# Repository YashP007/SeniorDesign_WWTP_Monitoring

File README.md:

# Advancing Wastewater Monitoring through Engineered Biological Sensors

**Yash Patel, Kara Walp**  
Department of Biomedical Engineering, Senior Design, Group 4 (2024–2025)  
Advisors: Rabia Tuğçe Yazicigil Kirby (BME, ECE), Miguel Jimenez (BME, MSE)

---

## Abstract
Effective industrial wastewater monitoring is critical for regulatory compliance and process optimization. However, traditional analytical techniques such as high-performance liquid chromatography (HPLC) are costly, require centralized facilities, and introduce significant latency between sampling and actionable results. Advances in synthetic biology have enabled the engineering of microbial whole-cell biosensors capable of detecting environmental contaminants with high specificity and rapid response times. Yet, practical deployment is limited by microbial instability in harsh environments and the lack of compact, low-power systems for low-signal optical outputs.

This work presents a deployable biosensing platform integrating a microbe housing and a low-power optical detection system designed for in situ wastewater monitoring. A membrane-based chamber enhances microbial viability by modulating nutrient and oxygen diffusion while preventing environmental microbial egress. Optical detection of luminescence was achieved using an analog front end with noise shaping and oversampling, enabling quantification of multiple biosensor outputs.

Experimental validation demonstrated improved microbial stability with Escherichia coli, extending viability beyond typical single-use constraints. The integrated system successfully captured optical responses from biosensors at environmentally relevant analyte concentrations. These findings highlight a promising pathway toward continuous, real-time wastewater monitoring using whole-cell biosensors. Future work must address challenges related to thermal robustness and variable contaminant backgrounds to achieve broader commercial deployment.

Contents:
Aim 1 - Creating a Microbe Housing for Deployment in Wastewater Treatment Plants
Aim 2 - Creating a Deployable Optical Detection Circuit

1. STL Files for Microbe Housing
2. Image Procesing Code for evaluating the microbe housing using the plate reader
3. KiCAD Files for Final Optical Sensing Circuit
4. Optical Sensing Circuit ESP32-C3 Microcontroller Program

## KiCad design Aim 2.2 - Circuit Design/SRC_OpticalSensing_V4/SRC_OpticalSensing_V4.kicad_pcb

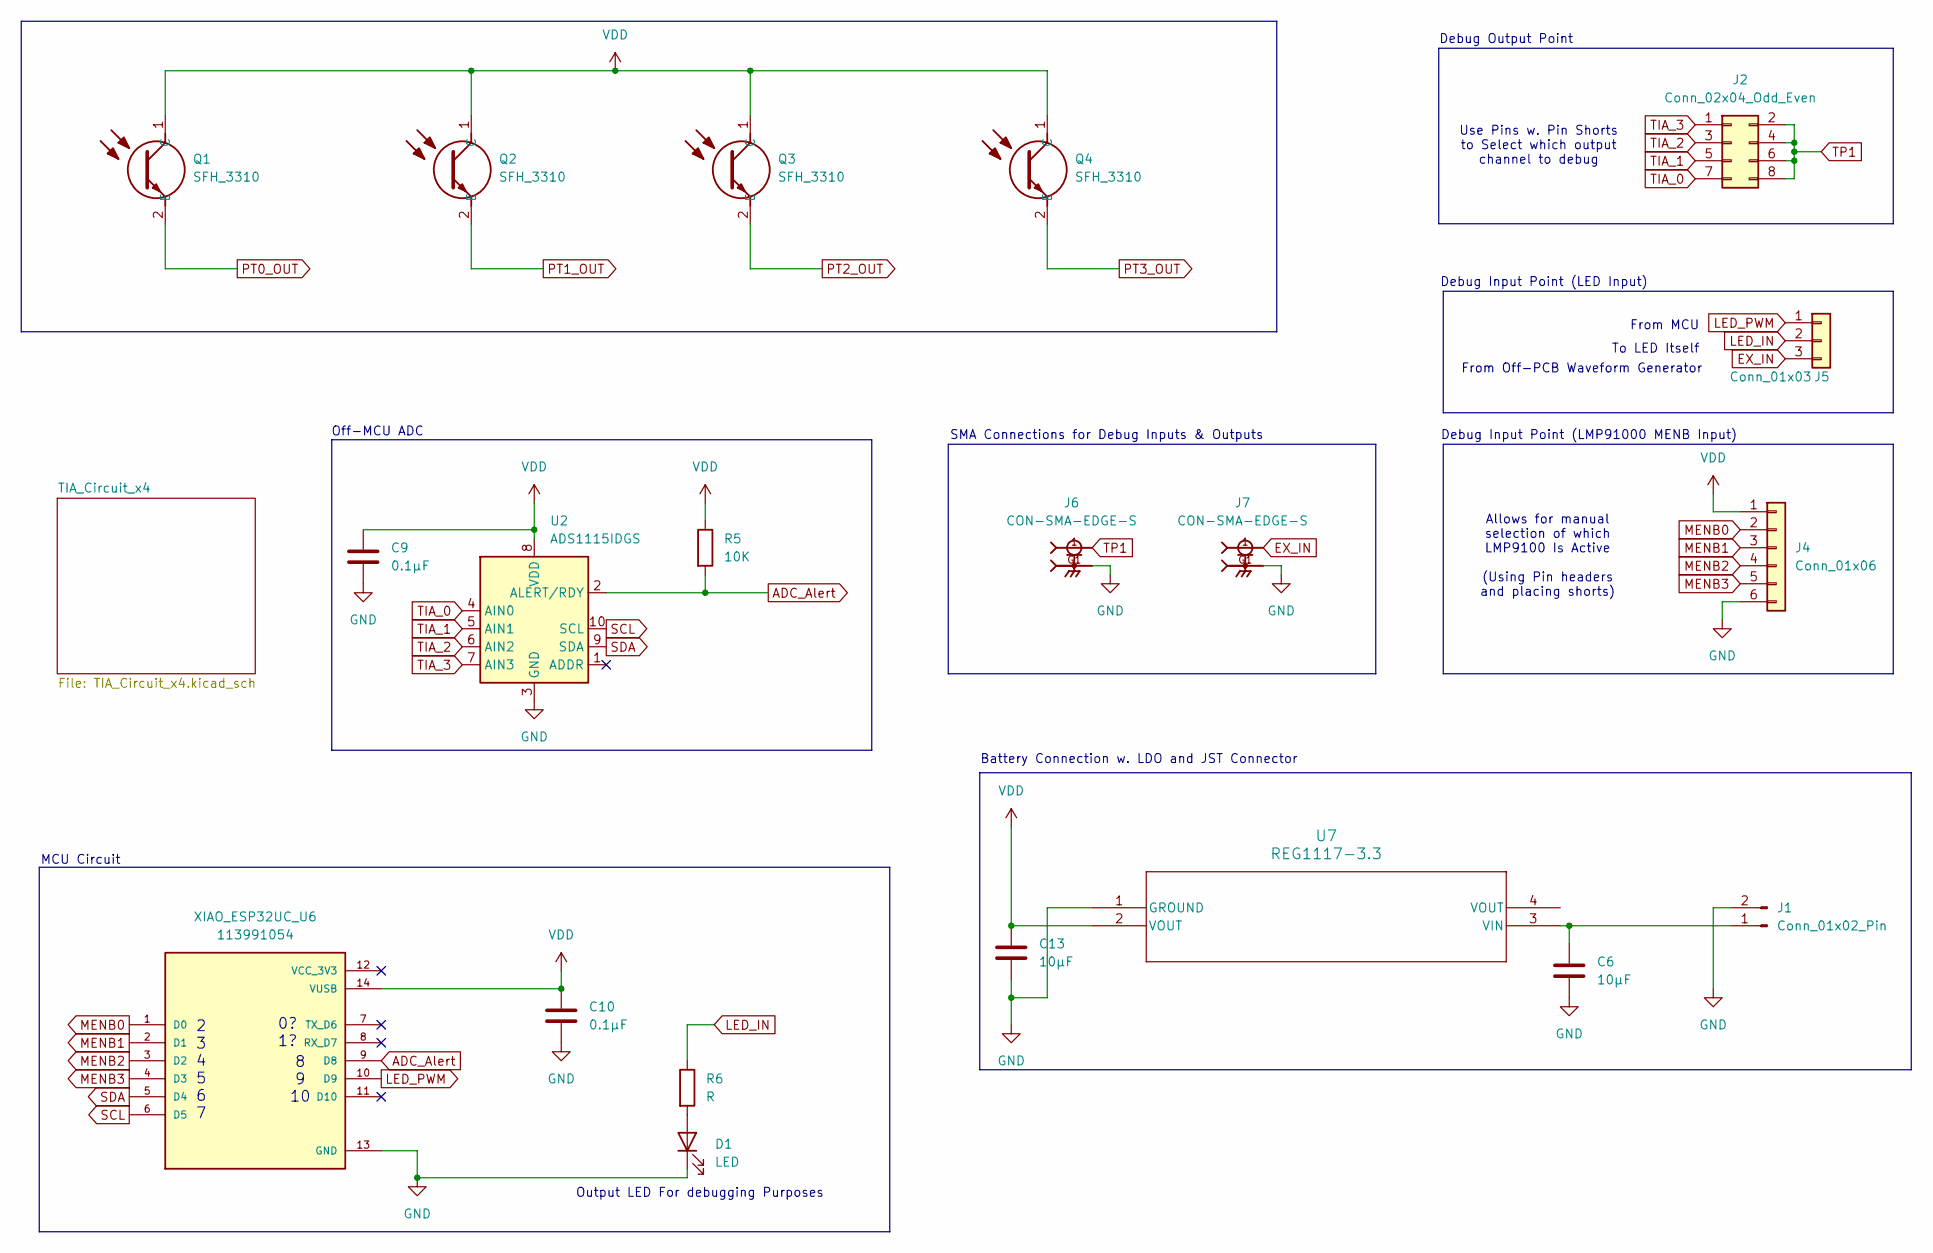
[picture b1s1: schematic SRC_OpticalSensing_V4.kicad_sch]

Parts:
C6, C13: 10µF; C_0805_2012Metric_Pad1.18x1.45mm_HandSolder
C9, C10: 0.1µF; C_0805_2012Metric_Pad1.18x1.45mm_HandSolder
D1: LED; LED_D5.0mm
J1: Conn_01x02_Pin; JWT_A3963_1x02_P3.96mm_Vertical
J2: Conn_02x04_Odd_Even; PinHeader_2x04_P2.54mm_Vertical
J4: Conn_01x06; PinHeader_1x06_P2.54mm_Vertical
J5: Conn_01x03; PinHeader_1x03_P2.54mm_Vertical
J6, J7: CON-SMA-EDGE-S; RFSOLUTIONS_CON-SMA-EDGE-S; PARTREV 1
Q1, Q2, Q3, Q4: SFH_3310; SFH3310; Mouser Part Number 720-SFH3310
R5: 10K; R_0805_2012Metric_Pad1.20x1.40mm_HandSolder
R6: R; R_0805_2012Metric_Pad1.20x1.40mm_HandSolder
U2: ADS1115IDGS; TSSOP-10_3x3mm_P0.5mm
U7: REG1117-3.3; DCY4
XIAO_ESP32UC_U6: 113991054; MODULE_113991054; PARTREV 23/05/2022

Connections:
ADC_Alert: R5.2, U2.2 (ALERT/RDY), XIAO_ESP32UC_U6.9 (D8)
EX_IN: J5.3, J7.1
GND: C6.2, C9.2, C10.2, C13.2, D1.1 (K), J1.2, J4.6, J6.G1, J7.G1, U2.3 (GND), U7.1 (GROUND), XIAO_ESP32UC_U6.13 (GND); also elsewhere on the board
LED_IN: J5.2, R6.1
LED_PWM: J5.1, XIAO_ESP32UC_U6.10 (D9)
MENB0: J4.2, XIAO_ESP32UC_U6.1 (D0); also elsewhere on the board
MENB1: J4.3, XIAO_ESP32UC_U6.2 (D1); also elsewhere on the board
MENB2: J4.4, XIAO_ESP32UC_U6.3 (D2); also elsewhere on the board
MENB3: J4.5, XIAO_ESP32UC_U6.4 (D3); also elsewhere on the board
unnamed: D1.2 (A), R6.2
unnamed: C6.1, J1.1, U7.3 (VIN)
PT0_OUT: Q1.2 (E); also elsewhere on the board
PT1_OUT: Q2.2 (E); also elsewhere on the board
PT2_OUT: Q3.2 (E); also elsewhere on the board
PT3_OUT: Q4.2 (E); also elsewhere on the board
SCL: U2.10 (SCL), XIAO_ESP32UC_U6.6 (D5); also elsewhere on the board
SDA: U2.9 (SDA), XIAO_ESP32UC_U6.5 (D4); also elsewhere on the board
TIA_0: J2.7, U2.4 (AIN0); also elsewhere on the board
TIA_1: J2.5, U2.5 (AIN1); also elsewhere on the board
TIA_2: J2.3, U2.6 (AIN2); also elsewhere on the board
TIA_3: J2.1, U2.7 (AIN3); also elsewhere on the board
TP1: J2.2, J2.4, J2.6, J2.8, J6.1
VDD: C9.1, C10.1, C13.1, J4.1, Q1.1 (C), Q2.1 (C), Q3.1 (C), Q4.1 (C), R5.1, U2.8 (VDD), U7.2 (VOUT), XIAO_ESP32UC_U6.14 (VUSB); also elsewhere on the board

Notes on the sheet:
Battery Connection w. LDO and JST Connector
6 7
Off-MCU ADC
From MCU
Use Pins w. Pin Shorts to Select which output channel to debug
Debug Input Point (LMP91000 MENB Input)
Allows for manual selection of which LMP9100 Is Active (Using Pin headers and placing shorts)
MCU Circuit
2 3 4 5
Debug Output Point
8 9 10
To LED Itself
SMA Connections for Debug Inputs & Outputs
0? 1?
Debug Input Point (LED Input)
From Off-PCB Waveform Generator
Output LED For debugging Purposes

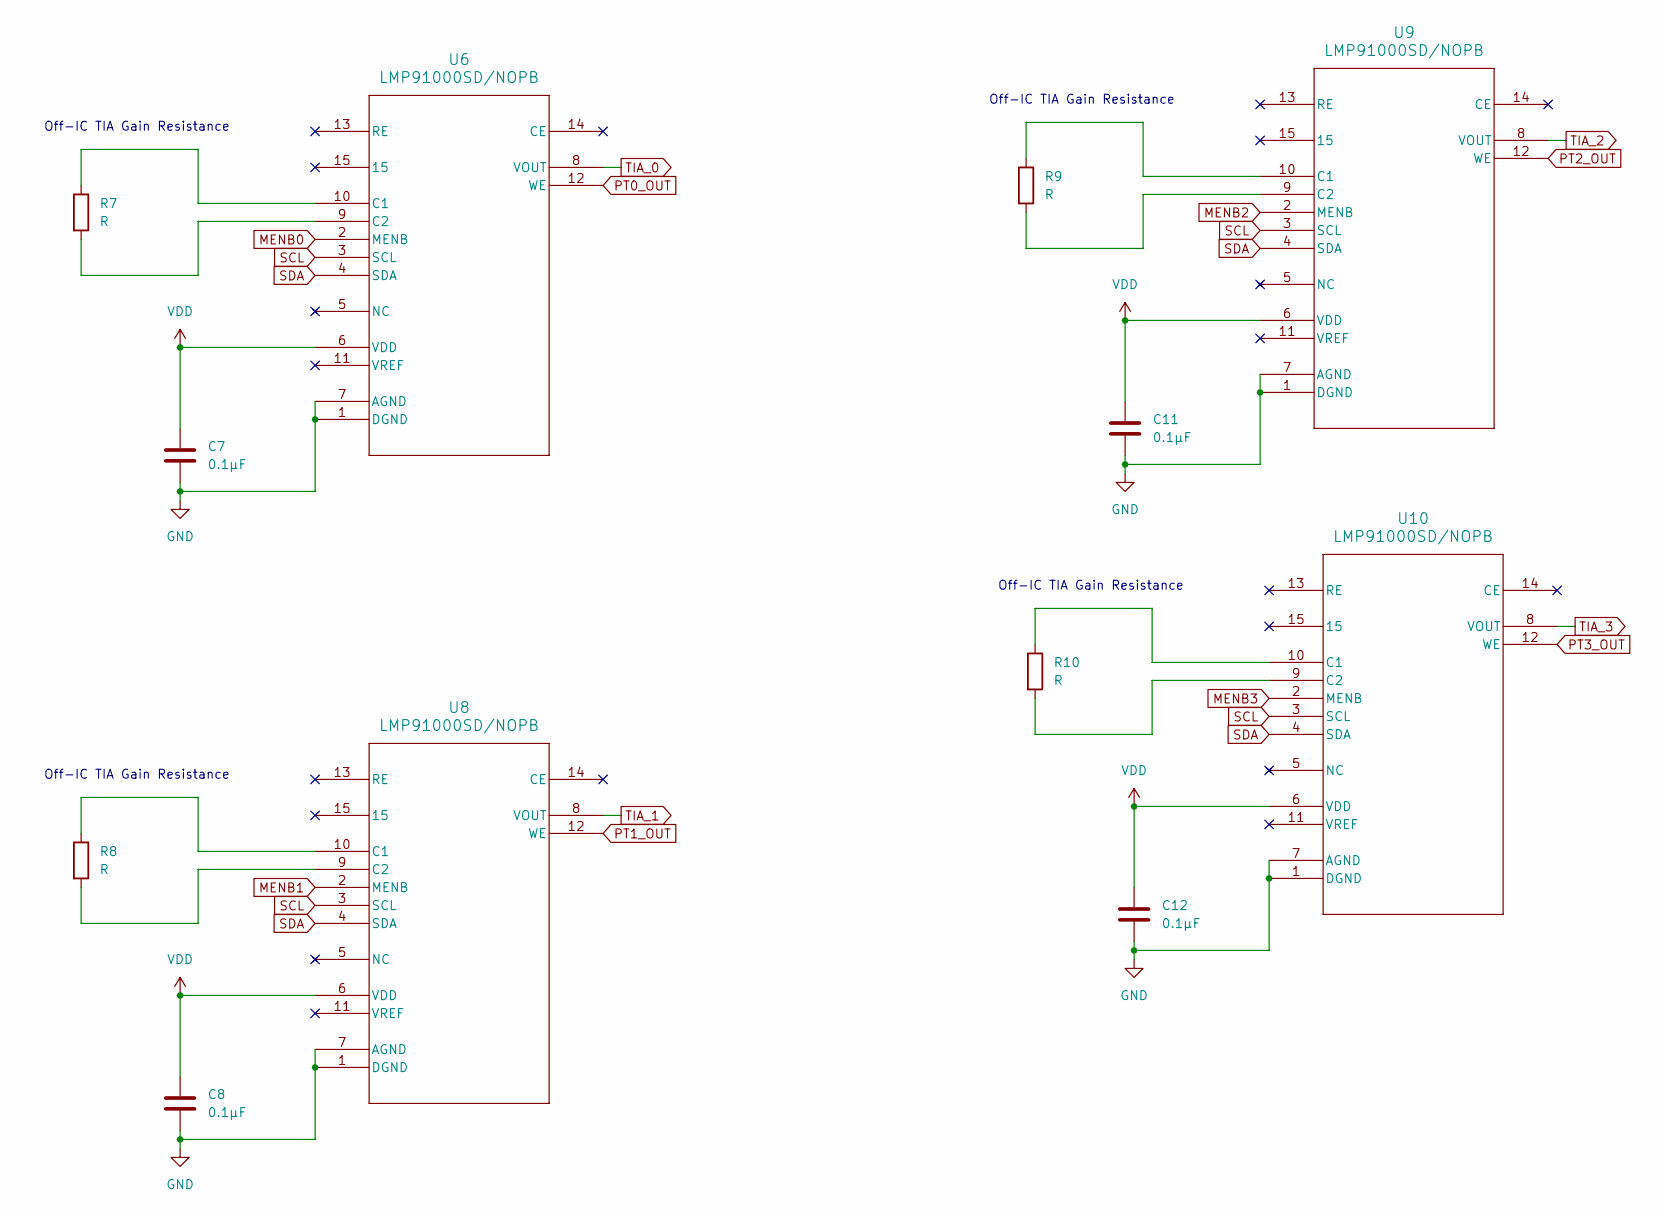
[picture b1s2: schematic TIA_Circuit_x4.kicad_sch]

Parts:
C7, C8, C11, C12: 0.1µF; C_0805_2012Metric_Pad1.18x1.45mm_HandSolder
R7, R8, R9, R10: R; R_0805_2012Metric_Pad1.20x1.40mm_HandSolder
U6, U8, U9, U10: LMP91000SD/NOPB; SDA14B

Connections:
GND: C7.2, C8.2, C11.2, C12.2, U6.1 (DGND), U6.7 (AGND), U8.1 (DGND), U8.7 (AGND), U9.1 (DGND), U9.7 (AGND), U10.1 (DGND), U10.7 (AGND); also elsewhere on the board
MENB0: U6.2 (MENB); also elsewhere on the board
MENB1: U8.2 (MENB); also elsewhere on the board
MENB2: U9.2 (MENB); also elsewhere on the board
MENB3: U10.2 (MENB); also elsewhere on the board
unnamed: R7.1, U6.10 (C1)
unnamed: R7.2, U6.9 (C2)
unnamed: R8.1, U8.10 (C1)
unnamed: R8.2, U8.9 (C2)
unnamed: R9.1, U9.10 (C1)
unnamed: R9.2, U9.9 (C2)
unnamed: R10.1, U10.10 (C1)
unnamed: R10.2, U10.9 (C2)
PT0_OUT: U6.12 (WE); also elsewhere on the board
PT1_OUT: U8.12 (WE); also elsewhere on the board
PT2_OUT: U9.12 (WE); also elsewhere on the board
PT3_OUT: U10.12 (WE); also elsewhere on the board
SCL: U6.3 (SCL), U8.3 (SCL), U9.3 (SCL), U10.3 (SCL); also elsewhere on the board
SDA: U6.4 (SDA), U8.4 (SDA), U9.4 (SDA), U10.4 (SDA); also elsewhere on the board
TIA_0: U6.8 (VOUT); also elsewhere on the board
TIA_1: U8.8 (VOUT); also elsewhere on the board
TIA_2: U9.8 (VOUT); also elsewhere on the board
TIA_3: U10.8 (VOUT); also elsewhere on the board
VDD: C7.1, C8.1, C11.1, C12.1, U6.6 (VDD), U8.6 (VDD), U9.6 (VDD), U10.6 (VDD); also elsewhere on the board

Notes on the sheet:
Off-IC TIA Gain Resistance

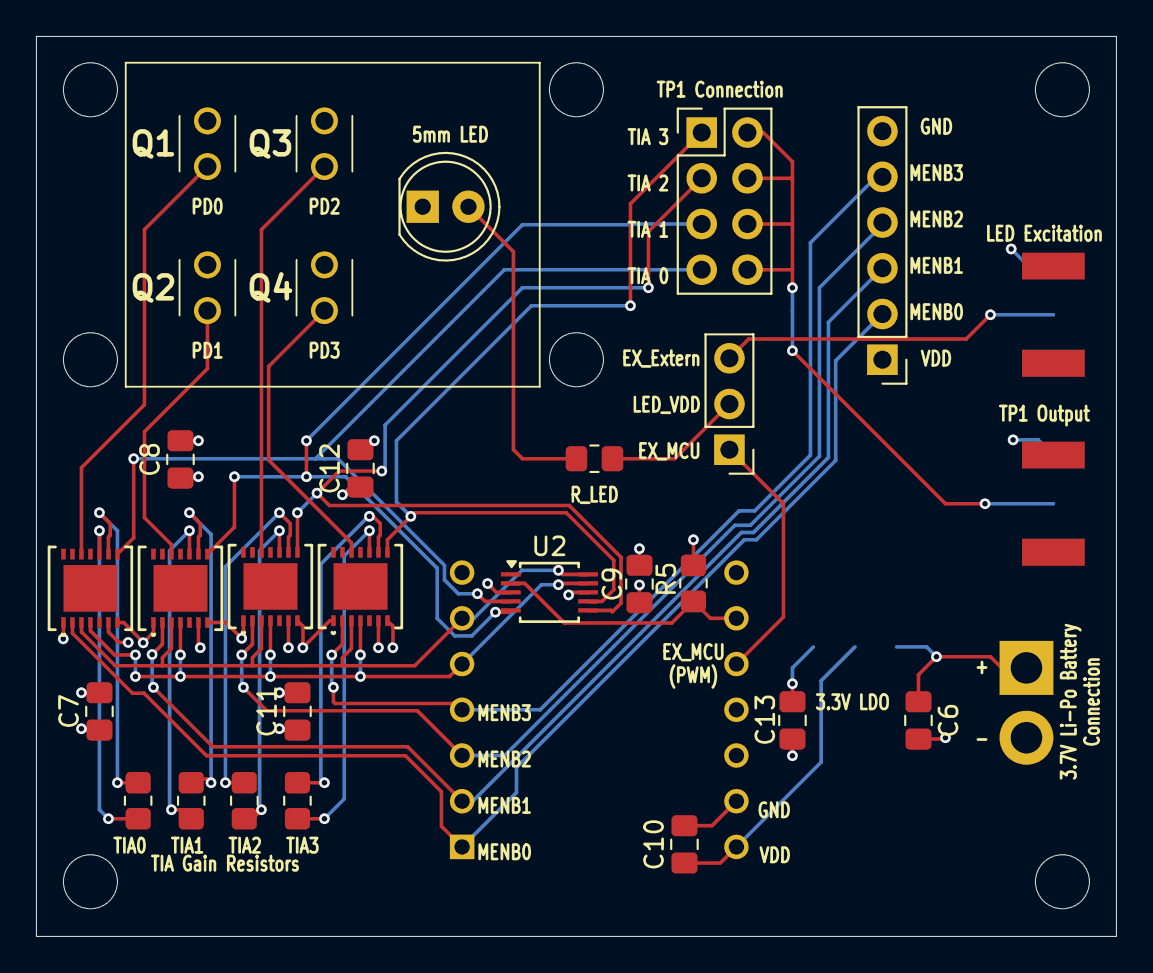
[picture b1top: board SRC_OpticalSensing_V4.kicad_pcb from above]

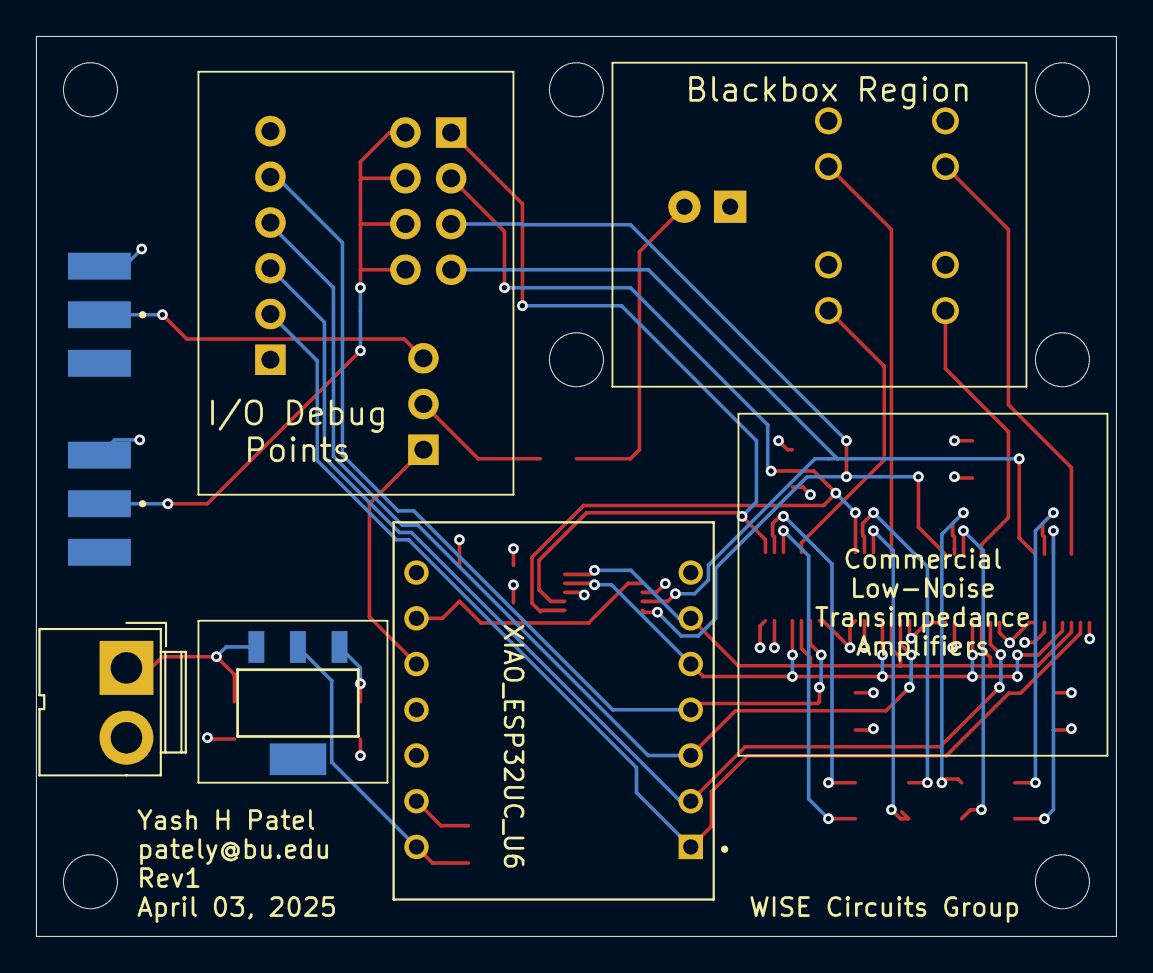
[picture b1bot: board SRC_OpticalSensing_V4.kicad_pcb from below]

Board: 4 copper layers, 60.0 x 50.0 mm, 32 parts (5 on the bottom side), 31 nets.

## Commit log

2025-04-29 added Yashs Portion of Files and Documentation
